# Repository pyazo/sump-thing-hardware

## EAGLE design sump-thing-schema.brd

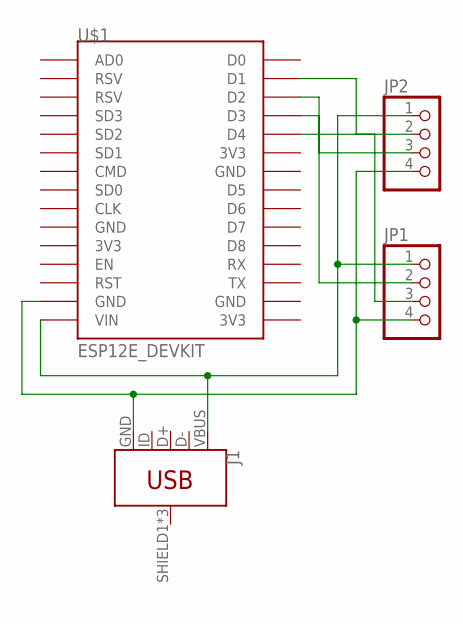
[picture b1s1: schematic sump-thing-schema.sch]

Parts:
J1: USB_MICRO-B_FEMALE-SMT; USB-B-MICRO-SMD
JP1, JP2: PINHD-1X4; 1X04
U$1: ESP12E_DEVKIT

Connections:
unnamed: J1.VBUS, JP1.1, JP2.1, U$1.VIN
unnamed: J1.GND, JP1.4, JP2.4, U$1.GND@1 (GND)
unnamed: JP2.2, U$1.D1
unnamed: JP2.3, U$1.D2
unnamed: JP1.2, U$1.D3
unnamed: JP1.3, U$1.D4

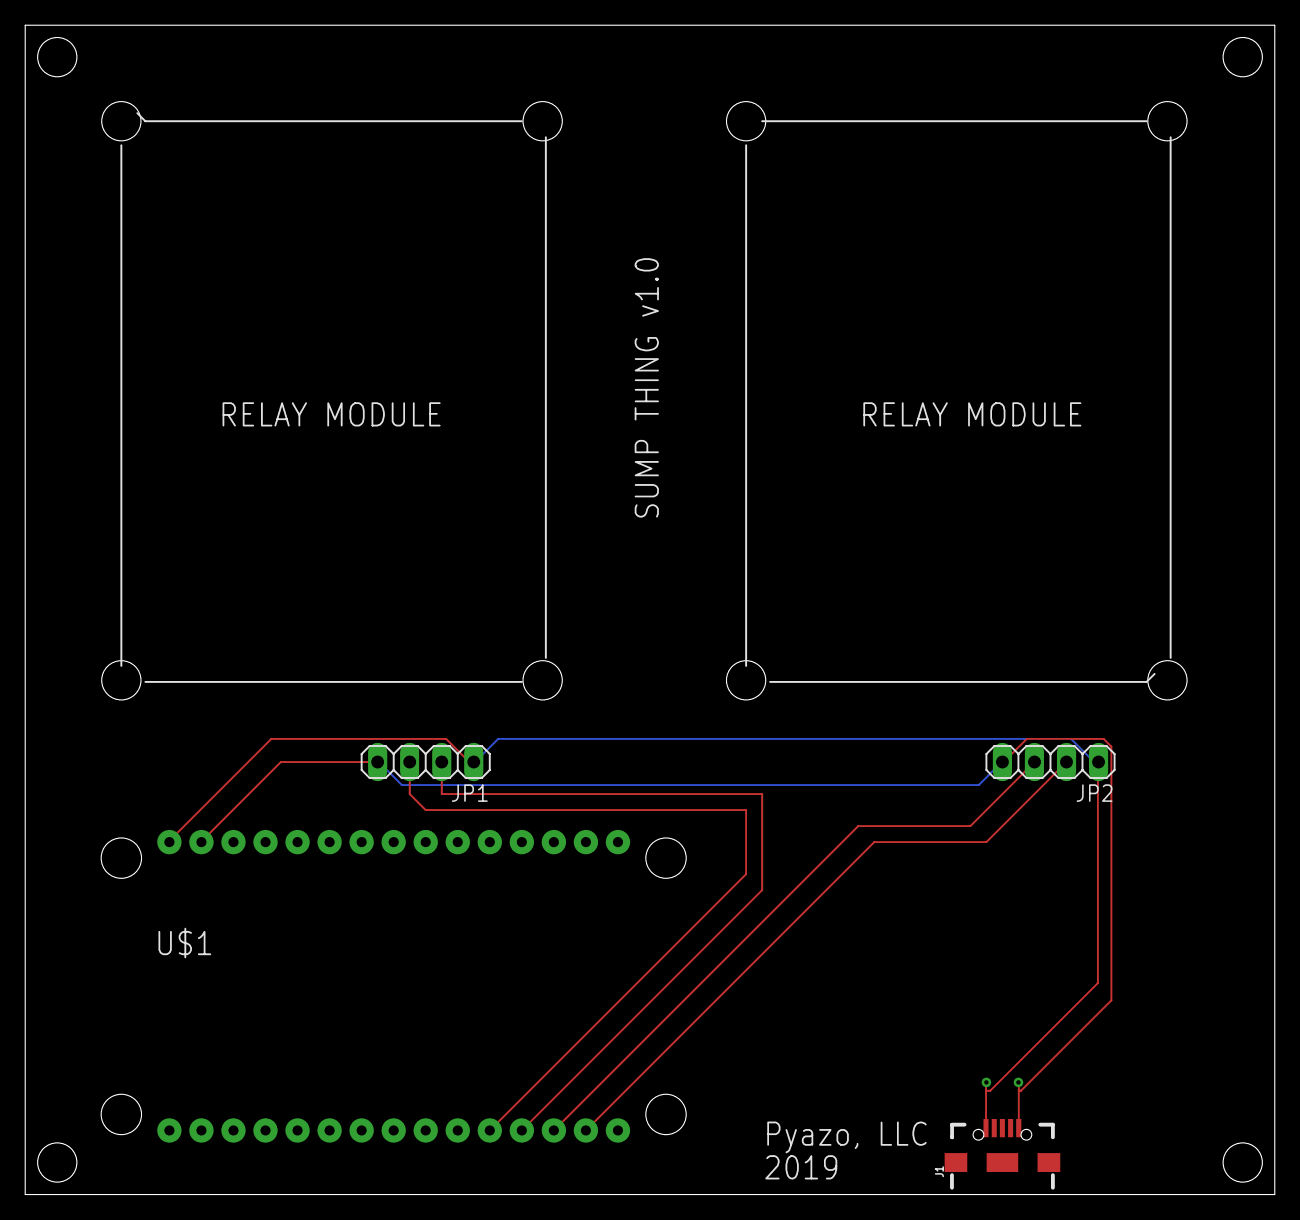
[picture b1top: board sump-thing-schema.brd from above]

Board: 2 copper layers, 99.1 x 92.7 mm, 4 parts (0 on the bottom side), 6 nets.

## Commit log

2019-05-06 Initial hardware design
2019-05-06 Add schema & board

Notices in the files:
parts and their libraries:
SparkFun-Connectors: Licensing: Creative Commons ShareAlike 4.0 International - https://creativecommons.org/licenses/by-sa/4.0
